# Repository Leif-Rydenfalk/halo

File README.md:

# halo — an open-source, cheaper AirTag-compatible tracker PCB

*A ce-designs project (`design:halo`) and a triad root. Started 2026-09-03.*

Leif, 2026-09-03, verbatim: *"its a clone of the apple airtag pcb but so we can
open source it and manufacture it for cheaper. do a whole lot of research and
find out a lot of open source projehcts which already tries to do this and
potential pcb designs and all available documentation and research out there
for this and place it all in this repo"*

Apple sells the AirTag for $29 with the hardware closed and the Find My network
gated behind an accessory program. This repo collects **everything public** about
the AirTag hardware, the Find My protocol, the open-source firmware that already
lets non-Apple boards ride the network (OpenHaystack and its successors), every
open coin-cell tracker PCB that could be a starting point, the chips that can
reproduce each function and what they cost, and the legal / certification /
child-safety / anti-stalking constraints — then designs an open board from it.

**Name.** "AirTag" and "Find My" are Apple trademarks, so the project is not
called that. *halo* — Leif, 2026-09-03: "a halo is always visible and you can
find it easily, which is what the project does." The project was briefly called
`haytag` (a tag for the haystack, after OpenHaystack); it was renamed on
2026-09-03 and GitHub redirects the old URL.

## What is where

```
README.md            this page
DECISIONS.md         every design question resolved by evidence, and what each option beat
MISSION.md           the definition of done: the eleven-artifact factory release pack
TOOLCHAIN.md         the tools we have, the open-source sim stack, the lanes building it
GOAL.md              what it is for — puck, embeddable block, local relative positioning (Leif's words)
research/            the dossiers — one per lane, every claim sourced with URL + date
  08-local-positioning-uwb-ble.md        peer-to-peer ranging: UWB TWR, BLE RSSI/AoA, open RTLS projects
  09-embeddable-block-and-modules.md     how to ship it as a KiCad sheet + castellated module
  01-airtag-hardware.md                  teardowns, chips, PCB, firmware, debug ports
  02-findmy-protocol-and-openhaystack.md the BLE payload, key rotation, every OSS project
  03-open-hardware-tag-designs.md        existing open PCBs (KiCad/Eagle/EasyEDA) ranked
  04-commercial-tags-and-clones.md       certified tags + AliExpress clones, what's inside
  05-components-and-cost-model.md        part candidates, BOM roll-up at 10/100/1k/10k
  06-legal-ip-certification-safety.md    trademark, patents, Find My program, DULT, FCC/CE, Reese's Law
  07-mechanical-enclosure-and-3d-models.md dimensions, speaker, battery door, open 3D models
  fetched/           raw text of the key pages, so the record survives link rot
  sources.tsv        every source any lane used: lane, url, title, date, note
reference/           vendored snapshots of the open-source repos (CLONE-LIST.tsv → MANIFEST.md)
  models/            freely-licensed 3D models and drawings
images/              teardown / FCC / design photos with CATALOG.md per folder (source + license)
spec/                machine-readable: bom-candidates.json, later specs.json
docs/                ANTI-STALKING.md and the design documents that follow
electronics/         schematic + netlist (ce-pcb) — next phase
hardware/            KiCad project — next phase
firmware/            pointers to upstream + our port — next phase
ce-parts/ ce-connections/ ce-assemblies/   the triad shelf for this design — next phase
evidence/            ledger.jsonl, append-only
out/                 renders, gerbers, reports — COMMITTED, they are data
```

## Method

1. **Research** (this commit) — collect every public fact with its source.
2. **Specify** — SPEC.md: what the clone must do (Find My via OpenHaystack keys
   first, official program path documented), the DULT anti-stalking minimum,
   target cost, target envelope (Ø ≈ 32 mm, 8 mm).
3. **Design** — ce-pcb board.py → KiCad → JLCPCB assembly; enclosure in ce-cad.
4. **Evidence** — every check lands in the ledger; the design is born T0.

## Status

Research lanes A–G running 2026-09-03. See research/ as they land.

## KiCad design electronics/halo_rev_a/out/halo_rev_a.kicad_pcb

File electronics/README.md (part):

# halo electronics — the circuit, block by block

*Lane B1. This describes **revision A**, which lives in `halo_rev_a/`. Every
number here was produced by a tool on this machine; the last section is the
list of things that were not, and it is the most important one.*

---

## Where everything is

| path | what |
|---|---|
| `halo_rev_a/schematic.py` | the circuit, generated. **The only place a part number is typed.** |
| `halo_rev_a/board.py` | the copper. Reads the netlist back out of the schematic — it is never retyped. |
| `halo_rev_a/footprints.py` | the six land patterns KiCad does not have, and the antenna geometry |
| `halo_rev_a/pinouts.json` | the nRF54L10 and LIS2DW12 pin tables, transcribed from the datasheets with citations |
| `halo_rev_a/sim/` | our own circuit and electromagnetic models |
| `halo_rev_a/out/` | the built `.kicad_sch`, `.kicad_pcb`, PDF, SVG, netlist, ERC and DRC reports |
| `../out/release/board/` | the factory package — Gerbers, BOM, CPL, stackup, verdicts |

Rebuild the whole thing:

```bash
cd ~/dev/ce-workshop
python3 ce-designs/halo/electronics/halo_rev_a/footprints.py
ce-pcb/bin/sch build ce-designs/halo/electronics/halo_rev_a/schematic.py \
                  -o ce-designs/halo/electronics/halo_rev_a/out
ce-pcb/bin/pcb   ce-designs/halo/electronics/halo_rev_a/board.py
ce-pcb/bin/sch erc ce-designs/halo/electronics/halo_rev_a/out/halo_rev_a.kicad_sch
```

---

## The circuit, in one paragraph

A CR2032 feeds an nRF54L10 directly. There is no buck, no LDO and no load
switch: the SoC's 1.7–3.6 V range spans the whole cell curve, so every
regulator in Apple's board is a part we do not buy. The SoC carries the
2.4 GHz radio, the NFC-A tag peripheral that drives an etched coil through two
tuning capacitors, and Bluetooth Channel Sounding for peer ranging. A
LIS2DW12TR on I²C wakes it on movement; a bare piezo bender bonded to the
shell is driven anti-phase from two GPIO with no amplifier; SWD comes out on
pads that cost no height.

---

## Block by block, and why each part is there

### 1. The SoC — `nRF54L10-QFAA-R7`, LCSC **C44800139**

QFN-48, 6 × 6 mm, 0.4 mm pitch. **$2.4012 at 1000.** DECISIONS.md D12 chose
it over the nRF52840 on a measurement: Bluetooth Channel Sounding gives 6–10 cm
mean error on coin-cell hardware, the same accuracy band as ultra-wideband,
from a radio already on the tag — and it costs **61 cents less** than the
nRF52832, where adding UWB costs $8.86 more.

Its datasheet numbers drive every power figure in this project: **TX 3.7 mA at
0 dBm, RX 2.1 mA, System-ON with 192 kB retained 2.4 µA** (Table 86). Those are
radio-only figures and lower than the 4.8 mA on Nordic's marketing page, which
is whole-device.

Decoupling is four 100 nF 0201s, one per VDD pin. The SoC's own DC/DC runs off
L1 between `DCC` and `DECD`; `DECA` is tied to `DECRF` because the datasheet
says *"Must be connected to DECA"*, not because it is tidy. The passive values
are Nordic's own reference circuit configuration 1 (Figure 175 / Table 82),
copied component-for-component — the correct move for an RF front end and the
wrong one to improvise.

### 2. Power, the cell, and the five-removals reset

The CR2032 lands on **three sprung fingers**, not a holder: SPEC.md §4 records
that the lowest-profile surface-mount retainer stands 2 mm above the board and
the stack has about 1.5 mm in total. Lane M's carrier holds the cell; the
board's job is three solder lands under the finger roots.

**Bulk is 4 × 10 µF 0402, not Apple's five 100 µF.** Two of the three loads
that needed 500 µF are gone — D12 deleted the U1 and D11a deleted the class-D
amplifier — and an 0805 is 1.25 mm tall against a 0.578 mm allowance. What
40 µF actually buys is measured, not asserted: see §"What the simulations
say".

**Cell-removal detection is a circuit, not a note.** SPEC.md §3 says the
AirTag has two positive contacts *"both sensed before boot"*, and the
five-removals factory reset needs the SoC to stay alive across a removal. So
the second positive finger is **sense-only**: it feeds a 4.7 M/4.7 M divider
into AIN0 whose bottom leg returns to a GPIO rather than to ground, so it
draws 0.32 µA *only while that pin is driven low* and nothing at all the rest
of the time. On a 2.4 µA sleep budget a permanently-on divider would have been
a 13 % battery-life tax. Pull the cell and the sense node collapses in about
0.24 ms while the bulk holds the rail up for seconds. Zero series loss, zero
extra silicon, and it uses the second finger for the reason Apple has one.

### 3. Clocks

32 MHz (`NX2016SA`, C843260) and 32.768 kHz (Epson `C32346`) crystals.
**External load capacitors are placed but NOT FITTED.** The nRF54L family has
on-die load capacitors on both oscillators; fitting external ones as well
double-loads the crystal and pulls it off frequency. The pads exist so a
crystal lot that does not pull in can be trimmed without a board spin, and
populating them means disabling the internal ones — a firmware change, not a
rework.

### 4. The 2.4 GHz path

Nordic's reference matching network (L2/C18/L3/C19/L4/C22/C23) from the `ANT`
pin to a 50 Ω node, then a **pi network — C20 shunt, L10 series, C21 shunt** —
between that node and the antenna feed. L10 is fitted as a 0 Ω jumper so the
board works untuned; all three are re-valued from a measured S11.

The pi is not decoration. A trace antenna on a Ø26 mm board with a Ø20 mm
battery can 0.578 mm underneath will not present 50 Ω, and **a matching network
is the only place that error can be absorbed.**

Two layout rules travel with this block, and they are Nordic's own words from
Figure 175: **C18's ground connects ONLY to pin 32 (VSS_PA), on the top
layer**, and **C19's ground must be isolated from every ground layer except the
bottom.** Both are written onto the sheet, because a schematic cannot enforce
them and forgetting them breaks the radio.

### 5. NFC — and there is no NFC chip

SPEC.md F8: the SoC's own NFC-A peripheral drives the coil from two pins.
**There is no separate NFC front end in an AirTag either**, which deletes a
BOM line most clone designs carry. The whole block is an etched coil and two
capacitors.

The coil is **2 turns, not 5**, and that is forced rather than chosen: the
usable annulus is R10.15–R10.85, because R10.0 is the cell can and R10.94 is
the nearest battery contact land minus clearance. At the 0.30 mm pitch a
0.127 mm process allows, 0.70 mm of band is 2.33 turns.

C24/C25 are **1.1 nF, and they were 130 pF until the solver corrected them.**
130 pF is Nordic's figure *for a 2 µH antenna*; ce-rf measured the real
winding at 0.2449 µH and returned 554.6 pF of tuning across it, so each series
capacitor is 1.109 nF.

### 6. There is no SPI NOR flash — a defect fix

Revision A carried a GD25LQ32EEIGR on VDD. **That part's supply range is
1.65–2.0 V and this board's only rail is a raw 3.0 V coin cell**, so it was out
of specification from the first second — the kind of fault that half-works on
a bench and fails in a field. Caught by the production test lane reading the
sheet.

Fitting a regulator was the alternative and it is what the real AirTag does. It
costs a part, an inductor, a rail, a test and board area, and buys nothing:
nothing else here wants 1.8 V. Meanwhile the firmware measures **13,164 bytes,
1.27 % of the SoC's own 1 MB**, and research/05 §3.7 already recommended
omitting it. So it is deleted. If revision B wants external firmware staging,
the part is a **wide-range low-power NOR such as the Macronix MX25R
(1.65–3.6 V)** — not another GD25LQ.

### 7. Motion — `LIS2DW12TR`, LCSC **C189624**

LGA-12, 2 × 2 mm, under 1 µA in low-power mode, **$0.7408 at 1000**. Apple's
BMA280 is unbuyable (29 in stock against a 10,000-piece minimum packet).

**On I²C, not SPI.** It costs two pins instead of four, frees the SPI bus for
the reserved UWB option, and lets the part answer while nothing else is
selected. CS is strapped high to select I²C and SA0 low to set address 0x18,
both through resistors rather than vias so a bring-up board can change mode.
Both interrupt lines are wired: INT1 is the wake line SPEC.md F7 needs, INT2
carries the orientation vector D12 attaches to every range.

### 8. The sounder — two pins, no amplifier

D11a: a bare **Murata 7BB-20-3** piezo bender, Ø20.0 × 0.22 mm, bonded to the
inside of the shell and driven anti-phase from two GPIO. This is Apple's trick
— make the housing the radiating surface — done with a catalogue part a fifth
of a millimetre thick, because the obvious buzzer is 3.5 mm tall and the stack
has 1.5 mm.

**No MAX98357A.** A bridge-tied class-D swings ±Vbat; two pins driven
anti-phase swing the same. What the amplifier buys is current, and a bender is
capacitive. That was research/05 §11.6's arithmetic; it is now measured.

R9 is 100 Ω of series damping and it earns its line — see below.

### 9. Debug and the reserved UWB option

Six SWD lands at 1.27 mm pitch. **A Tag-Connect was drawn first and does not
fit**: its land pattern is about 80 mm² with two NPTH alignment holes, and the
DRC found those holes drilled through the SoC's pads. Six 0.8 × 1.4 mm lands
carry the same six signals in 9 mm² with no holes.

J2 reserves the halo-uwb variant of D12 as **eight SMD lands** carrying SPI, an
interrupt, a reset and power — **not a DW3110 land pattern.** No document in
this repository carries the DW3110's pin assignment, and D9 forbids guessing
48 net names; and a second 6 × 6 mm QFN does not fit a Ø26 mm board whose
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
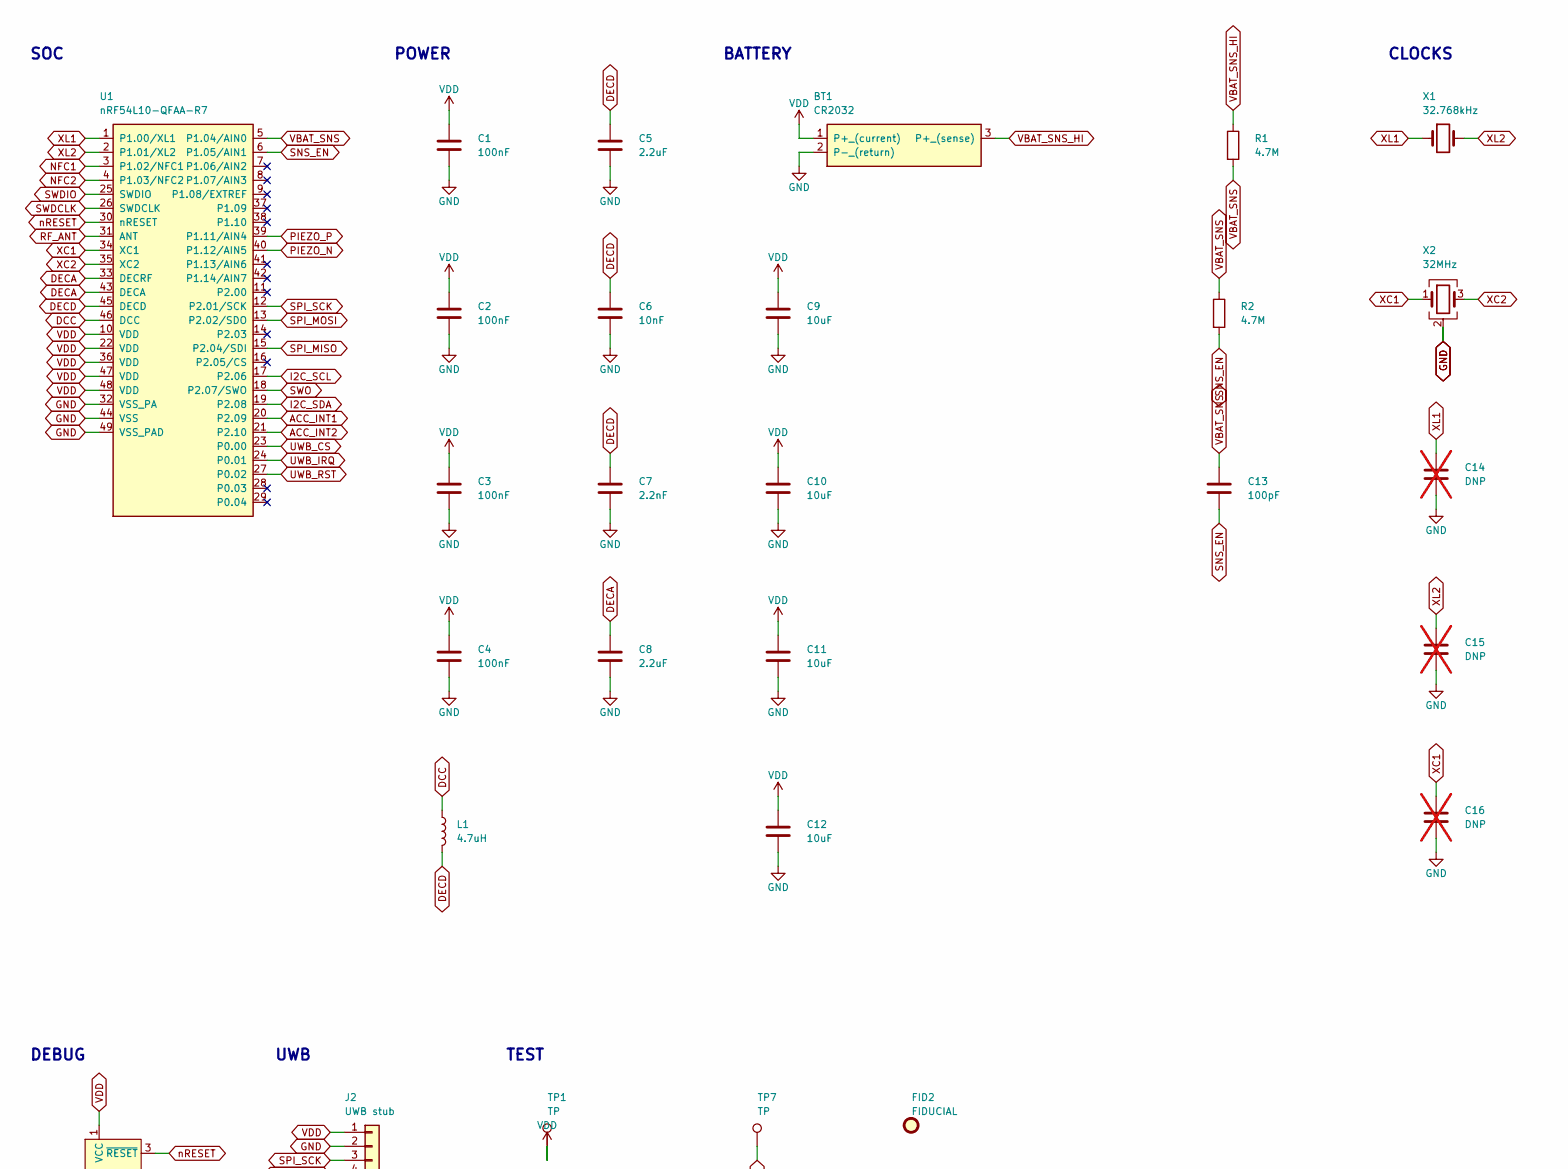
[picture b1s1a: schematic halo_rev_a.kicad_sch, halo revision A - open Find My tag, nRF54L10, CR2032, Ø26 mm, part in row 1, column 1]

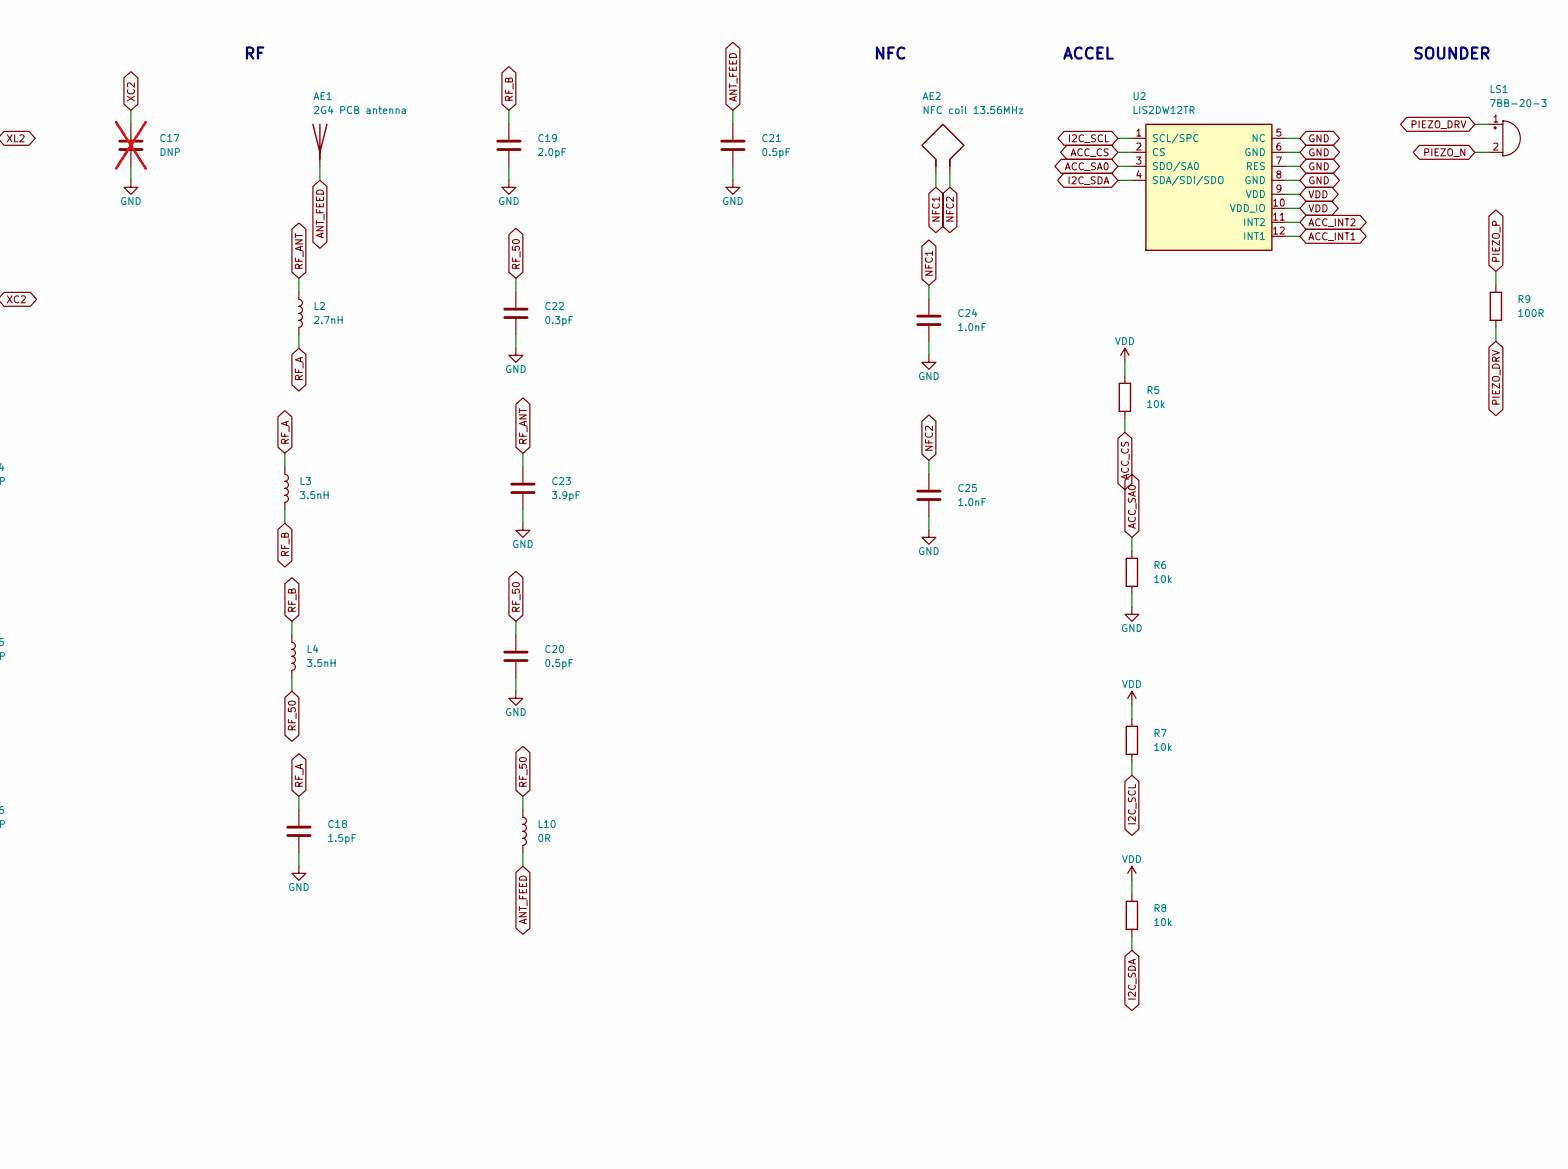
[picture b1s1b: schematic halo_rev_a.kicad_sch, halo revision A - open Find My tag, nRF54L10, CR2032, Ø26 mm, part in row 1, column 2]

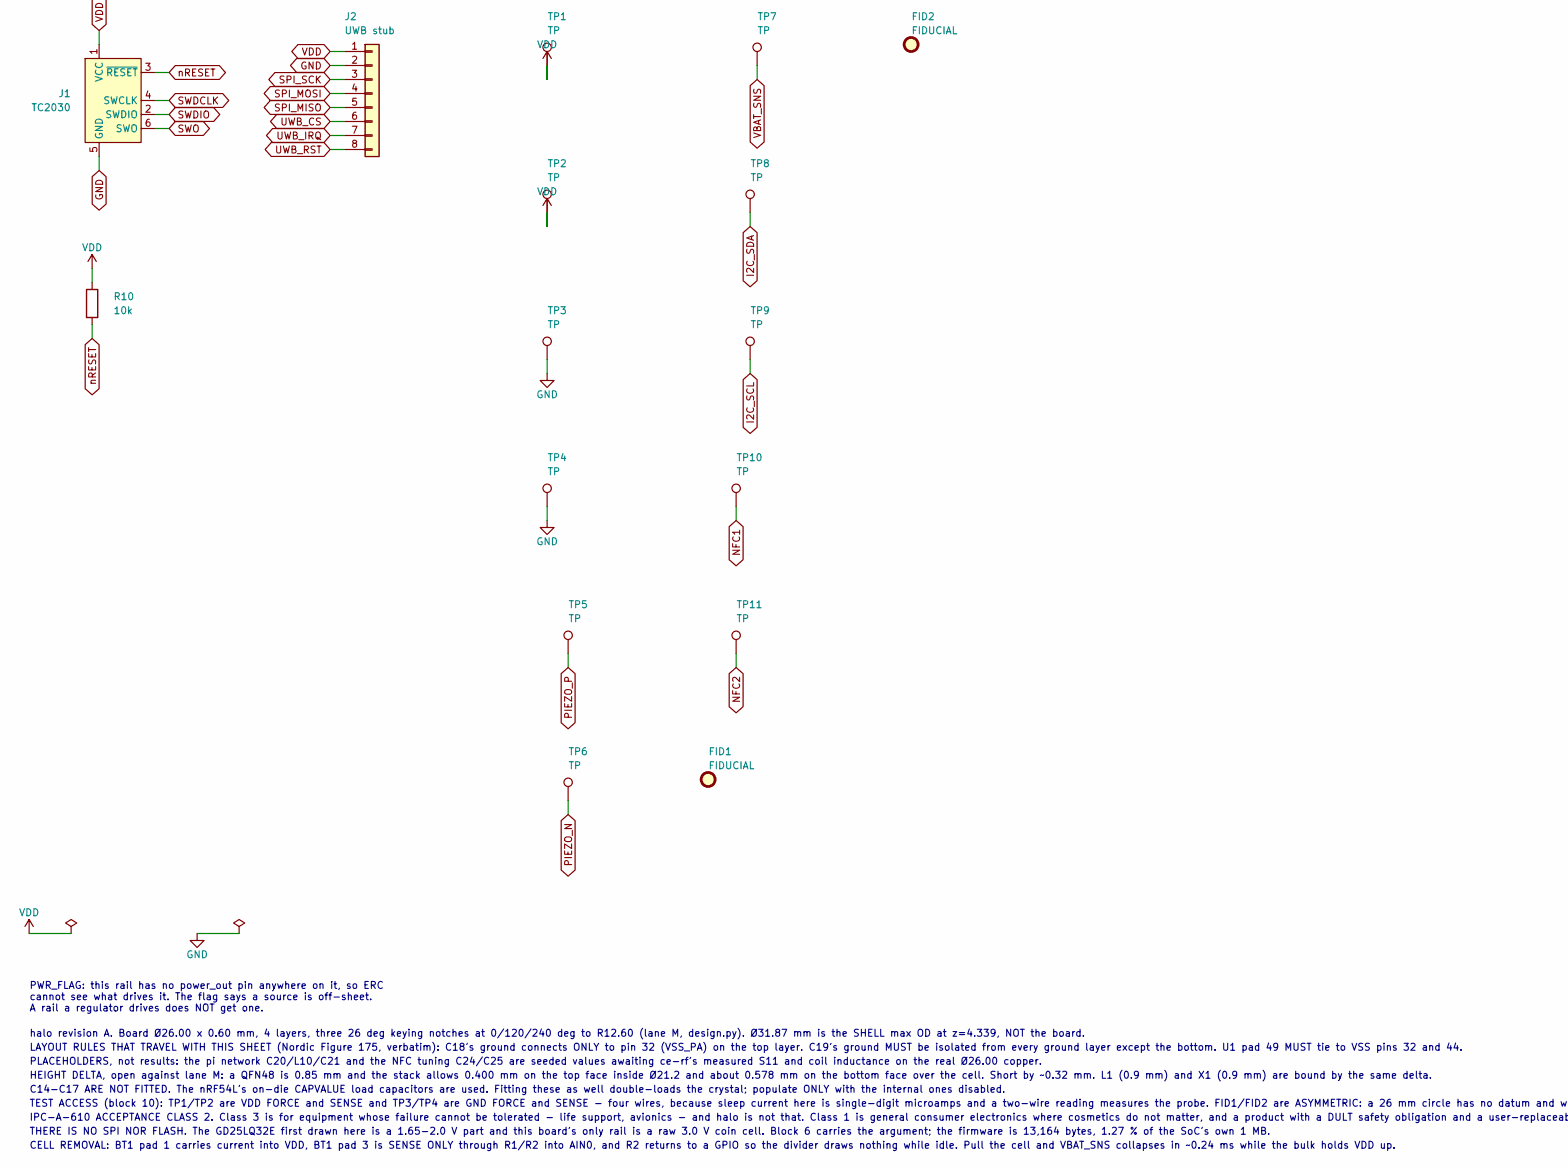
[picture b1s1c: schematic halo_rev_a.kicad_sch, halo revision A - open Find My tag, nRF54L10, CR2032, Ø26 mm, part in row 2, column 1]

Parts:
AE1: 2G4 PCB antenna
AE2: NFC coil 13.56MHz
BT1: CR2032; HALO_BATT_CONTACT_3PAD; MPN CR2032; LCSC Part # NO ORDER CODE - NOT AN SMT LINE
C1, C2, C3, C4: 100nF; C_0201_0603Metric; MPN TCC0201X5R104K100ZT; LCSC Part # C5142565
C5, C8: 2.2uF; C_0201_0603Metric; MPN GRM033R61A225KE47D; LCSC Part # C335106
C6: 10nF; C_0201_0603Metric; MPN GRM033R71A103KA01D; LCSC Part # C76941
C7: 2.2nF; C_0201_0603Metric; MPN GRM033R71A222KA01D; LCSC Part # C161479
C9, C10, C11, C12: 10uF; C_0402_1005Metric; MPN CL05A106MQ5NUNC; LCSC Part # C15525
C13: 100pF; C_0201_0603Metric; MPN GRM0335C1H101JA01D; LCSC Part # C76922
C14, C15, C16, C17: DNP; C_0201_0603Metric; not fitted
C18: 1.5pF; C_0201_0603Metric; MPN GJM0335C1E1R5WB01D; LCSC Part # C435397
C19: 2.0pF; C_0201_0603Metric; MPN GJM0335C1E2R0WB01D; LCSC Part # C668326
C20, C21: 0.5pF; C_0201_0603Metric; MPN GJM0335C1HR50WB01D; LCSC Part # C237424
C22: 0.3pF; C_0201_0603Metric; MPN GJM0335C1HR30WB01D; LCSC Part # C3904589
C23: 3.9pF; C_0201_0603Metric; MPN GJM0335C1E3R9WB01D; LCSC Part # C1852416
C24, C25: 1.0nF; C_0201_0603Metric; MPN GRM0335C1E102JA01D; LCSC Part # C161371
FID1, FID2: FIDUCIAL; Fiducial_0.5mm_Mask1mm; LCSC Part # n/a
J1: TC2030; Tag-Connect_TC2030-IDC-NL_2x03_P1.27mm_Vertical; LCSC Part # n/a
J2: UWB stub; HALO_UWB_LANDS_1x08_P1.00; LCSC Part # n/a
L1: 4.7uH; L_0603_1608Metric; MPN MLZ1608M4R7WT000; LCSC Part # C76799
L2: 2.7nH; L_0201_0603Metric; MPN LQP03HQ2N7B02D; LCSC Part # C7216765
L3, L4: 3.5nH; L_0201_0603Metric; MPN LQP03HQ3N5B02D; LCSC Part # C3911055
L10: 0R; L_0201_0603Metric; MPN 0201WMF0000TEE; LCSC Part # C473473
LS1: 7BB-20-3; MPN 7BB-20-3; LCSC Part # NOT IN CATALOGUE
R1, R2: 4.7M; R_0201_0603Metric; MPN 0201WMF4704TEE; LCSC Part # C778408
R5, R6, R7, R8, R10: 10k; R_0201_0603Metric; MPN 0201WMF1002TEE; LCSC Part # C473048
R9: 100R; R_0201_0603Metric; MPN 0201WMF1000TEE; LCSC Part # C270366
TP1, TP2, TP3, TP4, TP5, TP6, TP7, TP8, TP9, TP10, TP11: TP; HALO_TP_D0.8; LCSC Part # n/a
U1: nRF54L10-QFAA-R7; QFN-48-1EP_6x6mm_P0.4mm_EP4.4x4.4mm; MPN NRF54L10-QFAA-R7; LCSC Part # C44800139
U2: LIS2DW12TR; LGA-12_2x2mm_P0.5mm; MPN LIS2DW12TR; LCSC Part # C189624
X1: 32.768kHz; Crystal_SMD_3215-2Pin_3.2x1.5mm; MPN Q13FC13500049; LCSC Part # C95361
X2: 32MHz; Crystal_SMD_2016-4Pin_2.0x1.6mm; MPN NX2016SA-32MHZ-STD-CZS-5; LCSC Part # C843260

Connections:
ACC_CS: R5.2, U2.2 (CS)
ACC_INT1: U1.20 (P2.09), U2.12 (INT1)
ACC_INT2: U1.21 (P2.10), U2.11 (INT2)
ACC_SA0: R6.1, U2.3 (SDO/SA0)
ANT_FEED: AE1.1, C21.1, L10.2
DCC: L1.1, U1.46 (DCC)
DECA: C8.1, U1.33 (DECRF), U1.43 (DECA)
DECD: C5.1, C6.1, C7.1, L1.2, U1.45 (DECD)
I2C_SCL: R7.2, TP9.1, U1.17 (P2.06), U2.1 (SCL/SPC)
I2C_SDA: R8.2, TP8.1, U1.19 (P2.08), U2.4 (SDA/SDI/SDO)
NFC1: AE2.1, C24.1, TP10.1, U1.3 (P1.02/NFC1)
NFC2: AE2.2, C25.1, TP11.1, U1.4 (P1.03/NFC2)
PIEZO_DRV: LS1.1 (+), R9.2
PIEZO_N: LS1.2 (-), TP6.1, U1.40 (P1.12/AIN5)
PIEZO_P: R9.1, TP5.1, U1.39 (P1.11/AIN4)
RF_50: C20.1, C22.1, L4.2, L10.1
RF_A: C18.1, L2.2, L3.1
RF_ANT: C23.1, L2.1, U1.31 (ANT)
RF_B: C19.1, L3.2, L4.1
SNS_EN: C13.2, R2.2, U1.6 (P1.05/AIN1)
SPI_MISO: J2.5, U1.15 (P2.04/SDI)
SPI_MOSI: J2.4, U1.13 (P2.02/SDO)
SPI_SCK: J2.3, U1.12 (P2.01/SCK)
SWDCLK: J1.4 (SWCLK), U1.26 (SWDCLK)
SWDIO: J1.2 (SWDIO), U1.25 (SWDIO)
SWO: J1.6 (SWO), U1.18 (P2.07/SWO)
UWB_CS: J2.6, U1.23 (P0.00)
UWB_IRQ: J2.7, U1.24 (P0.01)
UWB_RST: J2.8, U1.27 (P0.02)
VBAT_SNS: C13.1, R1.2, R2.1, TP7.1, U1.5 (P1.04/AIN0)
VBAT_SNS_HI: BT1.3 (P+_(sense)), R1.1
XC1: C16.1, U1.34 (XC1), X2.1
XC2: C17.1, U1.35 (XC2), X2.3
XL1: C14.1, U1.1 (P1.00/XL1), X1.1
XL2: C15.1, U1.2 (P1.01/XL2), X1.2
nRESET: J1.3 (~RESET), R10.2, U1.30 (nRESET)

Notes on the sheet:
PWR_FLAG: this rail has no power_out pin anywhere on it, so ERC cannot see what drives it. The flag says a source is off-sheet. A rail a regulator drives does NOT get one.
SOC
POWER
BATTERY
CLOCKS
NFC
ACCEL
SOUNDER
DEBUG
UWB
TEST
halo revision A. Board Ø26.00 x 0.60 mm, 4 layers, three 26 deg keying notches at 0/120/240 deg to R12.60 (lane M, design.py). Ø31.87 mm is the SHELL max OD at z=4.339, NOT the board.
LAYOUT RULES THAT TRAVEL WITH THIS SHEET (Nordic Figure 175, verbatim): C18's ground connects ONLY to pin 32 (VSS_PA) on the top layer. C19's ground MUST be isolated from every ground layer except the bottom. U1 pad 49 MUST tie to VSS pins 32 and 44.
PLACEHOLDERS, not results: the pi network C20/L10/C21 and the NFC tuning C24/C25 are seeded values awaiting ce-rf's measured S11 and coil inductance on the real Ø26.00 copper.
HEIGHT DELTA, open against lane M: a QFN48 is 0.85 mm and the stack allows 0.400 mm on the top face inside Ø21.2 and about 0.578 mm on the bottom face over the cell. Short by ~0.32 mm. L1 (0.9 mm) and X1 (0.9 mm) are bound by the same delta.
C14-C17 ARE NOT FITTED. The nRF54L's on-die CAPVALUE load capacitors are used. Fitting these as well double-loads the crystal; populate ONLY with the internal ones disabled.
TEST ACCESS (block 10): TP1/TP2 are VDD FORCE and SENSE and TP3/TP4 are GND FORCE and SENSE - four wires, because sleep current here is single-digit microamps and a two-wire reading measures the probe. FID1/FID2 are ASYMMETRIC: a 26 mm circle has no datum and without them every pad position is a gu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
IPC-A-610 ACCEPTANCE CLASS 2. Class 3 is for equipment whose failure cannot be tolerated - life support, avionics - and halo is not that. Class 1 is general consumer electronics where cosmetics do not matter, and a product with a DULT safety obligation and a user-replaceable cell is not that either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
THERE IS NO SPI NOR FLASH. The GD25LQ32E first drawn here is a 1.65-2.0 V part and this board's only rail is a raw 3.0 V coin cell. Block 6 carries the argument; the firmware is 13,164 bytes, 1.27 % of the SoC's own 1 MB.
CELL REMOVAL: BT1 pad 1 carries current into VDD, BT1 pad 3 is SENSE ONLY through R1/R2 into AIN0, and R2 returns to a GPIO so the divider draws nothing while idle. Pull the cell and VBAT_SNS collapses in ~0.24 ms while the bulk holds VDD up.

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
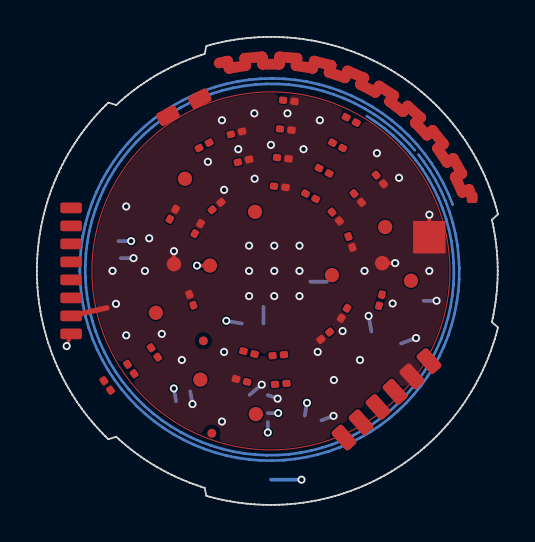
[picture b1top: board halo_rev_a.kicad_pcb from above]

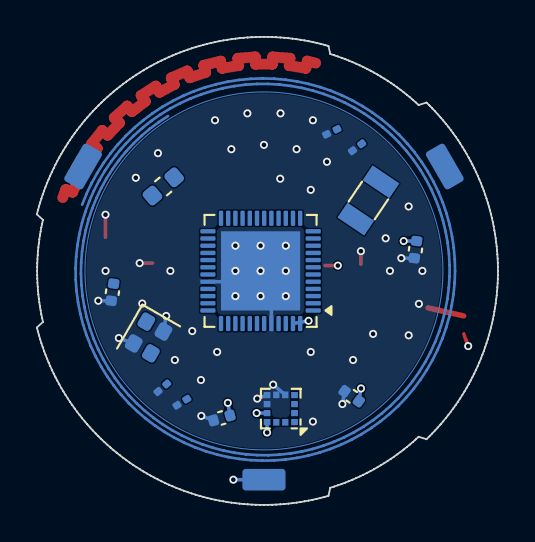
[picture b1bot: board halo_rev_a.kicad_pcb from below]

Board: 4 copper layers, 25.6 x 26.0 mm, 62 parts (15 on the bottom side), 38 nets.

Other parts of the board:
M1: HALO_SERIAL_MARK_1X8

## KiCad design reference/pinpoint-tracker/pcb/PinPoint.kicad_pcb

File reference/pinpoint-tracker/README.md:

# tracker
The PinPoint tracker module pcb and cad files

This repository contains all the KiCAD EDA files and Fusion 360 CAD designs for the PinPoint tracker modules

### Features
- nRF52832-based board - [Ebyte E73-2G4M08S1E](https://www.cdebyte.com/products/E73-2G4M08S1E/2)
- Compatible with Apple's FindMy network through [OpenHaystack](https://github.com/seemoo-lab/openhaystack)
- Small form factor (ideally less than 30x30x10mm)
- Location Pin shape
- RGB led for flair
- piezo buzzer for finding

### Repository structure
- `pcb/` contains the KiCAD EDA files for the tracker module
- `cad/` contains the Fusion 360 CAD files for the tracker module
- `docs/` contains the datasheets and other documentation for the components used in the tracker module
- `LICENSE` contains the license information for the repository
- `README.md` contains the information about the repository

### Board To-Do
- [x] battery holder
- [x] mounting holes
- [x] SWD connector
- [x] piezo buzzer
- [x] USB interface
- [x] RGB led
- [x] Push button

### License

This project is licensed under the TAPR Open Hardware License. See [LICENSE.txt](/LICENSE.txt) for more information.

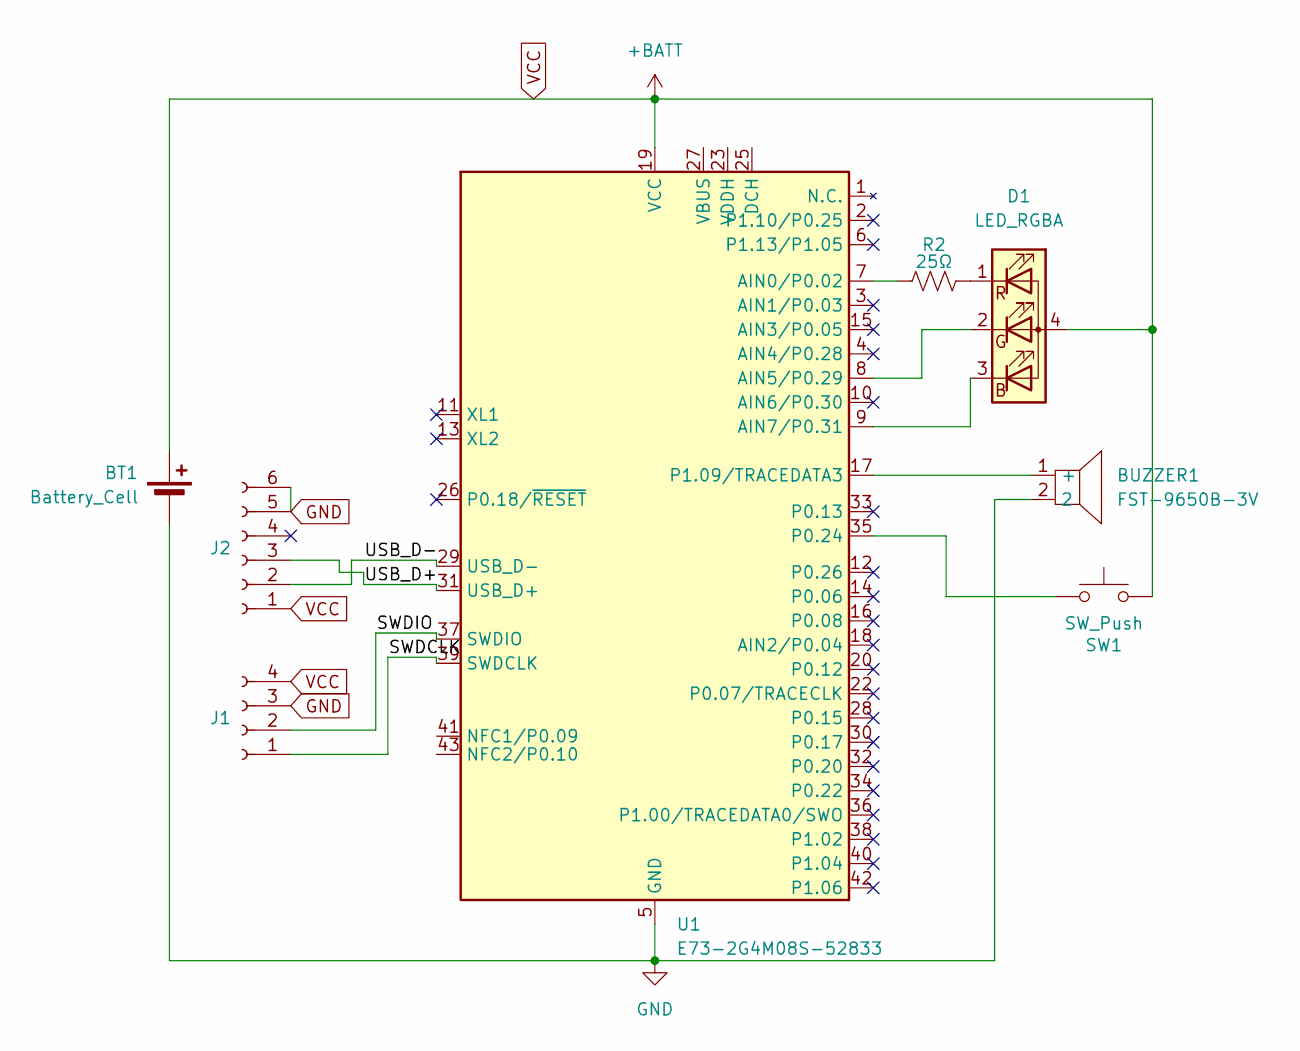
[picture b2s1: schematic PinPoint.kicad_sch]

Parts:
BT1: Battery_Cell; BatteryHolder_Keystone_3034_1x20mm; LCSC Part # C964823
BUZZER1: FST-9650B-3V; BUZ-SMD_L9.6-W9.6-LS10.0-R; LCSC Part C391032
D1: LED_RGBA; LED_LiteOn_LTST-C19HE1WT; LCSC Part # C458749
J1: PinHeader_1x04_P2.54mm_Vertical
J2: USB_Micro-B_Molex_47346-0001; LCSC Part # C132560
R2: 25Ω; R_0603_1608Metric
SW1: SW_Push; SW_SPST_CK_KXT3; LCSC Part # C388289
U1: E73-2G4M08S-52833; E73-2G4M08S1E; LCSC Part # C356849

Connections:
/SWDCLK: J1.1, U1.39 (SWDCLK)
/SWDIO: J1.2, U1.37 (SWDIO)
/USB_D+: J2.3, U1.31 (USB_D+)
/USB_D-: J2.2, U1.29 (USB_D-)
GND: BT1.2 (-), BUZZER1.2, J1.3, J2.5, J2.6, U1.5 (GND), U1.21 (GND), U1.24 (GND)
unnamed: BUZZER1.1 (+), U1.17 (P1.09/TRACEDATA3)
unnamed: D1.3 (BK), U1.9 (AIN7/P0.31)
unnamed: D1.2 (GK), U1.8 (AIN5/P0.29)
unnamed: D1.1 (RK), R2.2
unnamed: R2.1, U1.7 (AIN0/P0.02)
unnamed: SW1.1, U1.35 (P0.24)
VCC: BT1.1 (+), D1.4 (A), J1.4, J2.1, SW1.2, U1.19 (VCC)

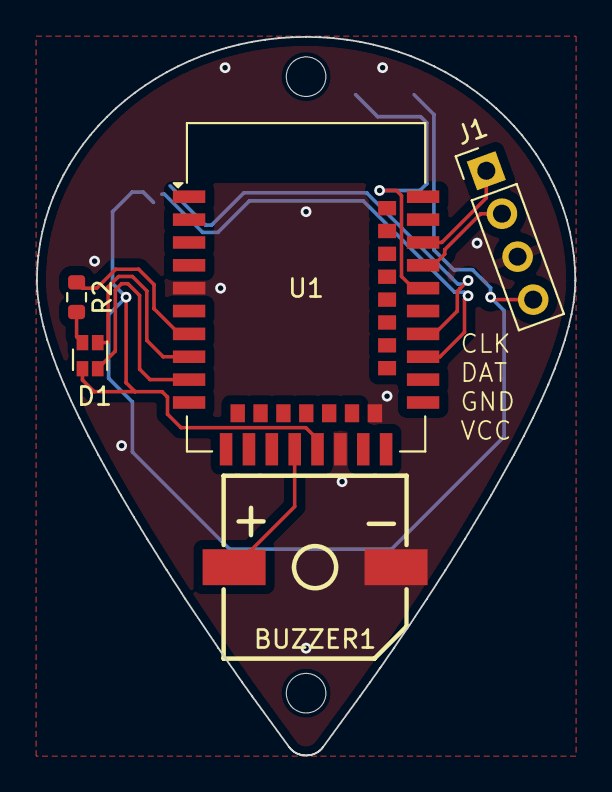
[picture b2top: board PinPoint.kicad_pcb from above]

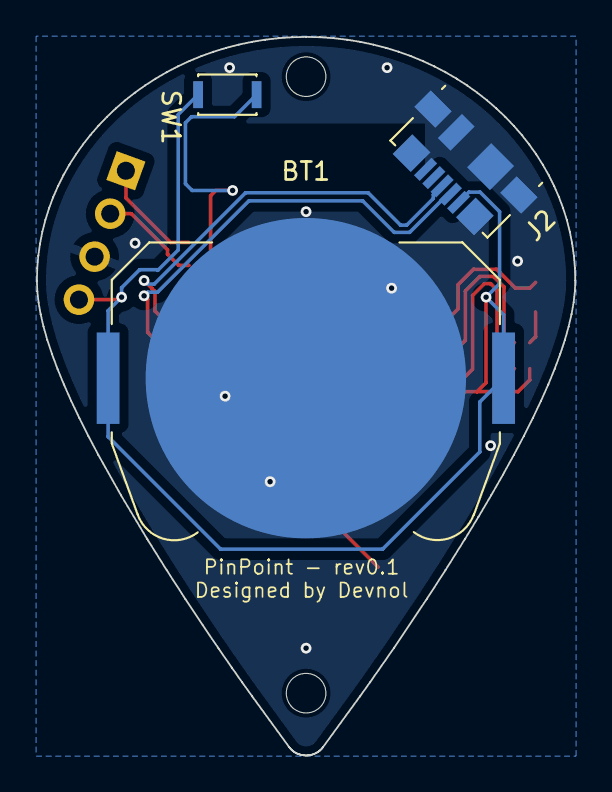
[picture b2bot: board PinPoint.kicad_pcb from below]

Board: 2 copper layers, 29.9 x 39.9 mm, 8 parts (3 on the bottom side), 12 nets.

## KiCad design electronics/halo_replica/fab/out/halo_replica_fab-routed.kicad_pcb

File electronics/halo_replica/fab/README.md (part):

# halo Replica — FAB VARIANT. The branch you can order.

## NOBODY HAS BUILT ONE.

This board has never been fabricated, never been populated, and never been powered on. Everything
below is a paper claim until one exists. Read that line before any other.

---

## What to upload

```
fab/out/halo_replica_jlc_0.8mm.zip     # the only thickness orderable at 4 layers — see below
```

The zip contains the 13 fabrication gerbers, the Excellon drill, the gerber job file, a **CPL**
(45 placements, on the drill file's origin), the **BOM**, and an `ORDER-SETTINGS.txt` naming every
setting to choose.

**There is no longer a 0.4 mm zip, and `g_package.py` refuses to write one for this board** — see
*Which one* below. `--allow-unorderable` overrides it for a different vendor.

### Bare board yes, assembly not yet

| | state |
|---|---|
| **bare board** | **ready** — gerbers + drill, `z_fabcheck` exit 0 |
| **assembly** | **NOT ready** — the BOM carries **4** real LCSC codes and **21** blank |

A blank LCSC cell is an **honest refusal**, not an oversight: no price pull was done for that line,
and each one names the exact MPN a human must look up. **Do not invent codes to fill them.**
JLCPCB's importer reads that column literally — a cell holding prose matches no part and **the line
is silently dropped from the assembly**, so the board comes back with parts missing. That is why
they are blank rather than explanatory.

**Which one: use the 0.8 mm zip at JLCPCB.** This was an open question in an earlier revision of
this file, which told you to *"try 0.4 first"*. **That advice was wrong and is withdrawn.**

**MEASURED 2026-09-05, in JLCPCB's live quote configurator**, not read off a capability page:

| layers selected | PCB Thickness offered |
|---|---|
| **4** | 0.8 · 1.0 · 1.2 · 1.6 · 2.0 — **0.4 and 0.6 are greyed out** |
| **2** | **0.4** · 0.8 · 1.0 · 1.2 · 1.6 · 2.0 — 0.6 greyed |

Both controls were run, because a greyed button and an unselected button look similar:

- **Negative control** — clicking `0.4mm` while 4 layers is selected changes nothing; the
  selection stays on 1.6 mm. It is genuinely disabled, not merely unstyled.
- **Positive control** — switching 4 → 2 layers **re-enables** `0.4mm` in the same page without a
  reload. The disable tracks the layer count, so it is a real constraint and not static styling.

**This board is 4 layers, so 0.4 mm is not orderable at JLCPCB. Order the 0.8 mm zip.**

Two further things the configurator did that a capability table does not tell you. Selecting
0.4 mm (at 2 layers) **forces the rest of the order**: `Surface Finish` jumps to **ENIG** with
**HASL greyed out** — you cannot hot-air-level a board that thin — `Material Type` collapses to
**FR4 TG135 alone**, and `Panel by JLCPCB` is refused. And it is not a small surcharge: the same
5-off order went from **$4.10 at 1.6 mm to ~$66** at 0.4 mm, the jump being an **engineering fee
$33 + via covering $16 + surface finish $16**. Thin is a different product, not a checkbox.

**If 0.4 mm matters more than the vendor does, PCBWay documents 0.40 mm at four layers**
("medium difficulty"). **That is a documentation claim only — it has NOT been put through
PCBWay's order form, so it is not the same grade of evidence as the table above.**

Settings: **4 layers · ENIG preferred · min trace/space 0.09 mm · min via 0.25 mm pad / 0.15 mm
drill** — all inside JLC's published four-layer capability.

---

## THIS IS NOT A 1:1 REPLICA, AND THE REASON IS A FORK RATHER THAN A COMPROMISE

> Apple's **WLCSP-50 fits** the ~6 mm annular ring and **cannot be landed**, because no complete
> ball map for it has ever been published. The **QFN-48 is the same die**, **can be landed**, and
> is **6 × 6 mm** — which does not fit that ring. **There is no arrangement that is both.**

This is the **buildable branch**. The **dimensional branch is `pcb/`**, which holds Apple's 25 mm
annulus at 0.30 mm with wafer-scale packages at measured positions — and **0 nets, 0 tracks, 0
vias**, because it is a transcription of photographs and not a circuit. Ordering *that* would give
you disconnected copper.

**A person holding a board that works but is the wrong shape should not have to work out why.**

### Every departure, with its reason

| | Apple | here | why |
|---|---|---|---|
| outline | Ø~25 mm **annulus** | **Ø30 mm disc** | a 6 mm QFN and a coin-cell holder need the area; still inside the AirTag's Ø31.9 mm shell |
| thickness | **0.30 mm** | **0.8 mm**, declared in the board file | 0.30 mm is below every 4-layer process we could find. **Measured**: JLCPCB greys out 0.4 and 0.6 mm at 4 layers, so 0.8 mm is the thinnest orderable. The board file now *says* 0.8 — it previously said **1.6 mm**, which is KiCad's default and nobody's decision, and it is the field a fabricator quotes from |
| SoC package | nRF52832 **WLCSP-50** | same die, **QFN-48** | no published ball map — 56 grid positions for 50 balls and **which six are depopulated is CANNOT DETERMINE** |
| 1.8 V rail | buck + load switch | **deleted; runs from the cell** | the nRF52832 spans 1.7–3.6 V across the whole CR2032 curve. It was also the highest-risk block on a board built to answer "does it work" |
| flash | GD25LQ32C | **MX25R3235F** | Apple's part is 1.65–2.0 V and **cannot run at 3 V**. This follows necessarily from the line above |
| load switch | FPF2487 | **MIC94090**, 0.5 µA | kept, because O'Flynn *measured* that the nRF controls flash power and the flash is off most of the time |
| UWB (U1/U2) | Apple U1 | **absent entirely** | never sold to anyone, at any price. A DNP part with a land pattern invites someone to try to buy one |
| antennas | 3, laser-structured on a moulded carrier | not reproduced | measured: they are **not on Apple's board** |
| passive values | unknown | **all CHOSEN from function** | a 100 nF and a 1 µF 0402 are visually identical — **no photograph can give a value** |
| five-removals reset | 3 sprung contacts, both positives sensed | **not reproduced** | a catalogue CR2032 holder has two terminals. A real loss of function, not a simplification |
| op-amp U7, regulator U9 | present | absent | U7's role is this project's *reconstruction*, not an observation; U9 is CANNOT DETERMINE down to its function |

---

## What a working board would and would not prove

**Would:** that the reconstruction of Apple's circuit is sound — that this arrangement of SoC,
flash, load switch, crystals and power path boots, advertises and runs from a coin cell.

**Would not:** that any value matches Apple's, that the RF match is right, or that an AirTag works
this way. Those are separate claims and none of them is tested by this board.

## Not verified

- **Nobody has built one.**
- **No LCSC part codes.** Every line carries a real manufacturer part number; a code with no pull
  date is a rumour. **JLC's own BOM tool will check stock in one click when you upload** — that
  question could not be answered from here without an account.
- The 2.4 GHz match **has never seen a VNA**. Fit `L1 = 0R` and leave the shunts off for a first
  article.
- The NFC capacitors assume a coil nobody has wound.
- The crystal load capacitors assume ~4 pF of stray on a board nobody has laid out.

## A designator warning

**`J1` and `U2` mean different parts on the two sheets.** On the **fab** sheet J1 is the sounder-coil
header and U2 is the load switch. On the **fidelity** sheet J1 is the coax receptacle and U2 is
Apple's UWB module. **Nobody may carry a designator between them.**

## Rebuild it yourself

```bash
bin/halo all          # sheet -> board -> DRC -> route -> pack, one verdict per stage
bin/halo status       # what exists, and is anything stale?
bin/halo doctor       # is everything reachable?
```

Exit code **is** the verdict: `0 PASS · 1 FAIL · 2 CANNOT DETERMINE`, and CANNOT
DETERMINE is not a pass. Individual stages are `bin/halo build|route|pack`.
The stages, what each answers, and the four traps the pipeline exists to
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
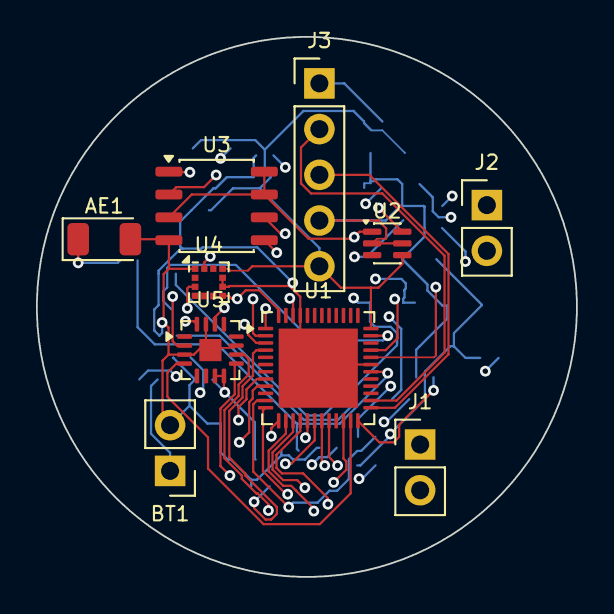
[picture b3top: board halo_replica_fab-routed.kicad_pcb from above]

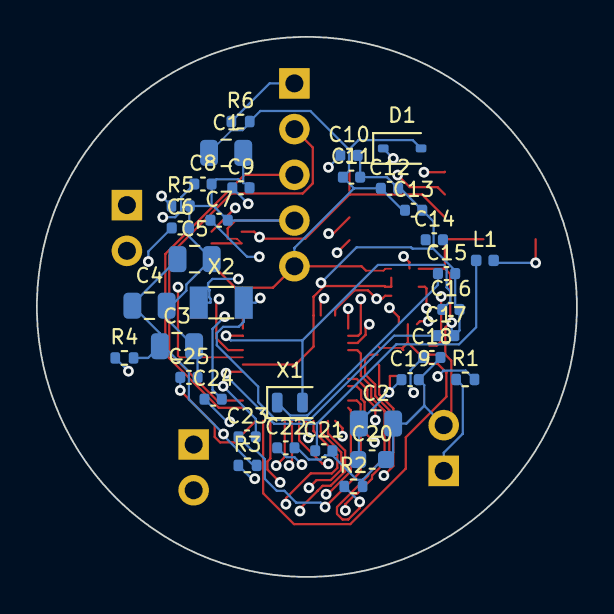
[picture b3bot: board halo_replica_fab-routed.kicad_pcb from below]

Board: 4 copper layers, 30.0 x 30.0 mm, 45 parts (35 on the bottom side), 37 nets.

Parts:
AE1: 2450AT18A100 2.4GHz chip; Johanson_2450AT18x100
BT1: CR2032 CELL - OFF-BOARD, ON 2 PADS; PinHeader_1x02_P2.54mm_Vertical
C1, C2, C3, C4, C5: 100uF 6.3V X5R; C_0805_2012Metric
C6, C10: 1uF 16V X7R; C_0402_1005Metric
C7, C8, C9, C11, C12, C13, C19, C25: 100nF 16V X7R; C_0402_1005Metric
C14: DNP - see note; C_0402_1005Metric
C15, C16: 8pF 50V C0G; C_0402_1005Metric
C17, C18: 22pF 50V C0G; C_0402_1005Metric
C20: 10uF 6.3V X5R; C_0603_1608Metric
C21, C22: 1.0pF 50V C0G; C_0402_1005Metric
C23, C24: 150pF 50V C0G; C_0402_1005Metric
D1: BAT54HT1G (Vf~0.24V @1mA); D_SOD-323
J1: VOICE COIL / SOUNDER; PinHeader_1x02_P2.54mm_Vertical
J2: NFC COIL 13.56MHz; PinHeader_1x02_P2.54mm_Vertical
J3: SWD (nRST SWDIO SWCLK GND VBAT); PinHeader_1x05_P2.54mm_Vertical
L1: 3.9nH; L_0402_1005Metric
R1, R2: 10M; R_0402_1005Metric
R3, R4, R6: 10k; R_0402_1005Metric
R5: 100k; R_0402_1005Metric
U1: nRF52832-QFAA-R; QFN-48-1EP_6x6mm_P0.4mm_EP4.4x4.4mm
U2: MIC94090YC6 (0.5 uA, 1.5 A); SOT-363_SC-70-6
U3: MX25R3235F 32Mb 1.65-3.6V; JEITA_SOIC-8_3.9x4.9mm_P1.27mm
U4: SC7A20 3-axis, LGA-12; LGA-12_2x2mm_P0.5mm
U5: MAX98357A class-D, TQFN-16; TQFN-16-1EP_3x3mm_P0.5mm_EP1.23x1.23mm
X1: 32MHz 10ppm CL=8pF; Crystal_SMD_2012-2Pin_2.0x1.2mm
X2: 32.768kHz 20ppm CL=12.5pF; Crystal_SMD_3215-2Pin_3.2x1.5mm

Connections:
ACC_INT1: U1.10, U4.5
ACC_SCL: R3.1, U1.8, U4.12
ACC_SDA: R4.1, U1.9, U4.2
AMP_GAIN: R5.1, U5.2
AMP_nSD: U1.23, U5.4
ANT_FEED: AE1.1, C22.1, L1.2
ANT_SOC: C21.1, L1.1, U1.30
DEC1: C7.1, U1.1
DEC2: C8.1, U1.32
DEC3: C9.1, U1.33
DEC4: C10.1, U1.46
FLASH_PWR_EN: U1.15, U2.6
FLASH_nCS: U1.14, U3.1
GND: AE1.2, BT1.2, C1.2, C2.2, C3.2, C4.2, C5.2, C6.2, C7.2, C8.2, C9.2, C10.2, C11.2, C12.2, C13.2, C15.2, C16.2, C17.2, C18.2, C19.2, C20.2, C21.2, C22.2, C25.2, J3.4, R2.2, R5.2, U1.31, U1.45, U1.49, U2.2, U2.5, U3.4, U4.1, U4.8, U4.9, U5.3, U5.11, U5.15, U5.17
I2S_BCLK: U1.16, U5.16
I2S_DIN: U1.22, U5.1
I2S_LRCLK: U1.17, U5.14
NFC1: C23.1, U1.11
NFC2: C24.1, U1.12
NFC_COIL_A: C23.2, J2.1
NFC_COIL_B: C24.2, J2.2
SPI_MISO: U1.18, U3.2
SPI_MOSI: U1.19, U3.5
SPI_SCK: U1.20, U3.6
SPK_N: J1.2, U5.10
SPK_P: J1.1, U5.9
SWDCLK: J3.3, U1.25
SWDIO: J3.2, U1.26
VBAT: C1.1, C2.1, C3.1, C4.1, C5.1, C11.1, C12.1, C13.1, C19.1, C20.1, D1.2, J3.5, R3.2, R4.2, R6.2, U1.13, U1.36, U1.48, U2.4, U4.3, U4.7, U4.10, U5.7, U5.8
VBAT_RAW: BT1.1, D1.1, R1.1
VBAT_SENSE: R1.2, R2.1, U1.4
VFLASH: C6.1, U2.1, U3.3, U3.7, U3.8
XC1: C15.1, U1.34, X1.1
XC2: C16.1, U1.35, X1.2
XL1: C17.1, U1.2, X2.1
XL2: C18.1, U1.3, X2.2
nRESET: C25.1, J3.1, R6.1, U1.24

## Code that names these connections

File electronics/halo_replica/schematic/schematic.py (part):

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        s.net("GND", "U1." + pad)

    # The DEC/DCC network. TOPOLOGY ONLY - see the sheet text.
    for ref, pad, note in (("C14", "1", "DEC1, pin 1"),
                           ("C15", "32", "DEC2, pin 32"),
                           ("C16", "33", "DEC3, pin 33"),
                           ("C17", "46", "DEC4, pin 46")):
        net = {"C14": "DEC1", "C15": "DEC2", "C16": "DEC3",
               "C17": "DEC4"}[ref]
        s.part(ref, "Device:C", value="CANNOT DETERMINE", group="soc",
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    s.part("L2", "Device:L", value="DC/DC L - CANNOT DETERMINE",
           group="soc", footprint=L0402,
           fields=B("R/C/L bulk", "PLACEHOLDER-L12",
                    "The nRF52832's own DC/DC runs DCC (pin 47) through an "
                    "inductor into DEC4 (pin 46). NOT INDEPENDENTLY SOURCED "
                    "HERE - it is the family arrangement, and this repository "
                    "holds no copy of the reference circuit to check it "
                    "against. WHETHER APPLE ENABLED THE DC/DC AT ALL IS "
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      "is NO separate NFC chip in an AirTag - that deletes a line most clone "
      "BOMs carry.")
    N("NFC2", INFERRED, "U1.12 (NFC2/P0.10)", "C7", "Same.")
    N("NFC_COIL_A", INFERRED, "C6", "ANT2 pin 1", "Series tuning into the "
      "coil. See ANT2's open conflict about what that annulus actually is.")
    N("NFC_COIL_B", INFERRED, "C7", "ANT2 pin 2", "Same.")
    s.net("NFC1", "U1.11", "C6.1")
    s.net("NFC2", "U1.12", "C7.1")
    s.net("NFC_COIL_A", "C6.2", "ANT2.1")
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                    "their hands - and LOW for anything geometric. The "
                    "magnet (bom.json SPK-MAGNET) is mechanical and carries "
                    "no net, so it is not on this sheet."))
    N("SPK_P", INFERRED, "U5 OUTP", "LS1 pin 1; R9 (sense divider)",
      "A class-D bridge drives the coil differentially. Inferred from the "
      "part family.")
    N("SPK_N", INFERRED, "U5 OUTN", "LS1 pin 2", "Same.")
    s.net("SPK_P", "U5.9", "LS1.1", "R9.1")
    s.net("SPK_N", "U5.10", "LS1.2")

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
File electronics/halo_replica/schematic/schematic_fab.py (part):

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                    "board is not that shell. A 2-pin header takes any coil "
                    "or magnetic transducer so the audio path can be tested "
                    "on a bench before anyone builds an enclosure."))
    N("SPK_P", "U5 OUTP", "J1 pin 1", "Bridge output, one side.")
    N("SPK_N", "U5 OUTN", "J1 pin 2", "Bridge output, other side.")
    s.net("SPK_P", "U5.9", "J1.1")
    s.net("SPK_N", "U5.10", "J1.2")

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      "The NFC-A tag peripheral is the SoC's own. THERE IS NO NFC CHIP - "
      "that is the single best thing this design inherits from Apple's.")
    N("NFC2", "U1.12 (NFC2/P0.10)", "C24", "As NFC1.")
    N("NFC_COIL_A", "C23", "J2 pin 1", "Series tuning into the coil.")
    N("NFC_COIL_B", "C24", "J2 pin 2", "As NFC_COIL_A.")
    s.net("NFC1", "U1.11", "C23.1")
    s.net("NFC2", "U1.12", "C24.1")
    s.net("NFC_COIL_A", "C23.2", "J2.1")
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                    "'try it out if it works' is impossible. Apple exposes "
                    "SWD on bare test pads and locks it with APPROTECT; this "
                    "is a header, unlocked, because it is ours."))
    N("nRESET", "U1.24 (P0.21/nRESET)", "J3 pin 1", "SWD reset.")
    N("SWDIO", "U1.26", "J3 pin 2", "SWD data.")
    N("SWDCLK", "U1.25", "J3 pin 3", "SWD clock.")
    s.net("nRESET", "U1.24", "J3.1")
    s.net("SWDIO", "U1.26", "J3.2")
    s.net("SWDCLK", "U1.25", "J3.3")
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
    s.part("R6", "Device:R", value="10k", group="test", footprint=R0402,
           fields=F("R/C/L bulk", "RC0402FR-0710KL",
                    "Pull-up on nRESET so the pin does not float. The "
                    "nRF52832 has an internal one, and an external one costs "
                    "a fraction of a microamp and removes a class of "
                    "bring-up mystery."))
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    s.part("C25", "Device:C", value="100nF 16V X7R", group="test",
           footprint=C0402,
           fields=F("R/C/L bulk", "CL05B104KO5NNNC",
                    "nRESET debounce, and it makes a scope probe on the pin "
                    "meaningful."))
    s.net("nRESET", "C25.1")
    s.net("GND", "C25.2")
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

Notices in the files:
electronics/halo_rev_a/out/halo_rev_a.kicad_sch:
Leif-Rydenfalk/halo - CERN-OHL-S
